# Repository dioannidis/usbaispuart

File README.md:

# USBaispUART

( version 5 )

   A single side, through hole, USBa(i)sp clone, designed in Kicad 5.

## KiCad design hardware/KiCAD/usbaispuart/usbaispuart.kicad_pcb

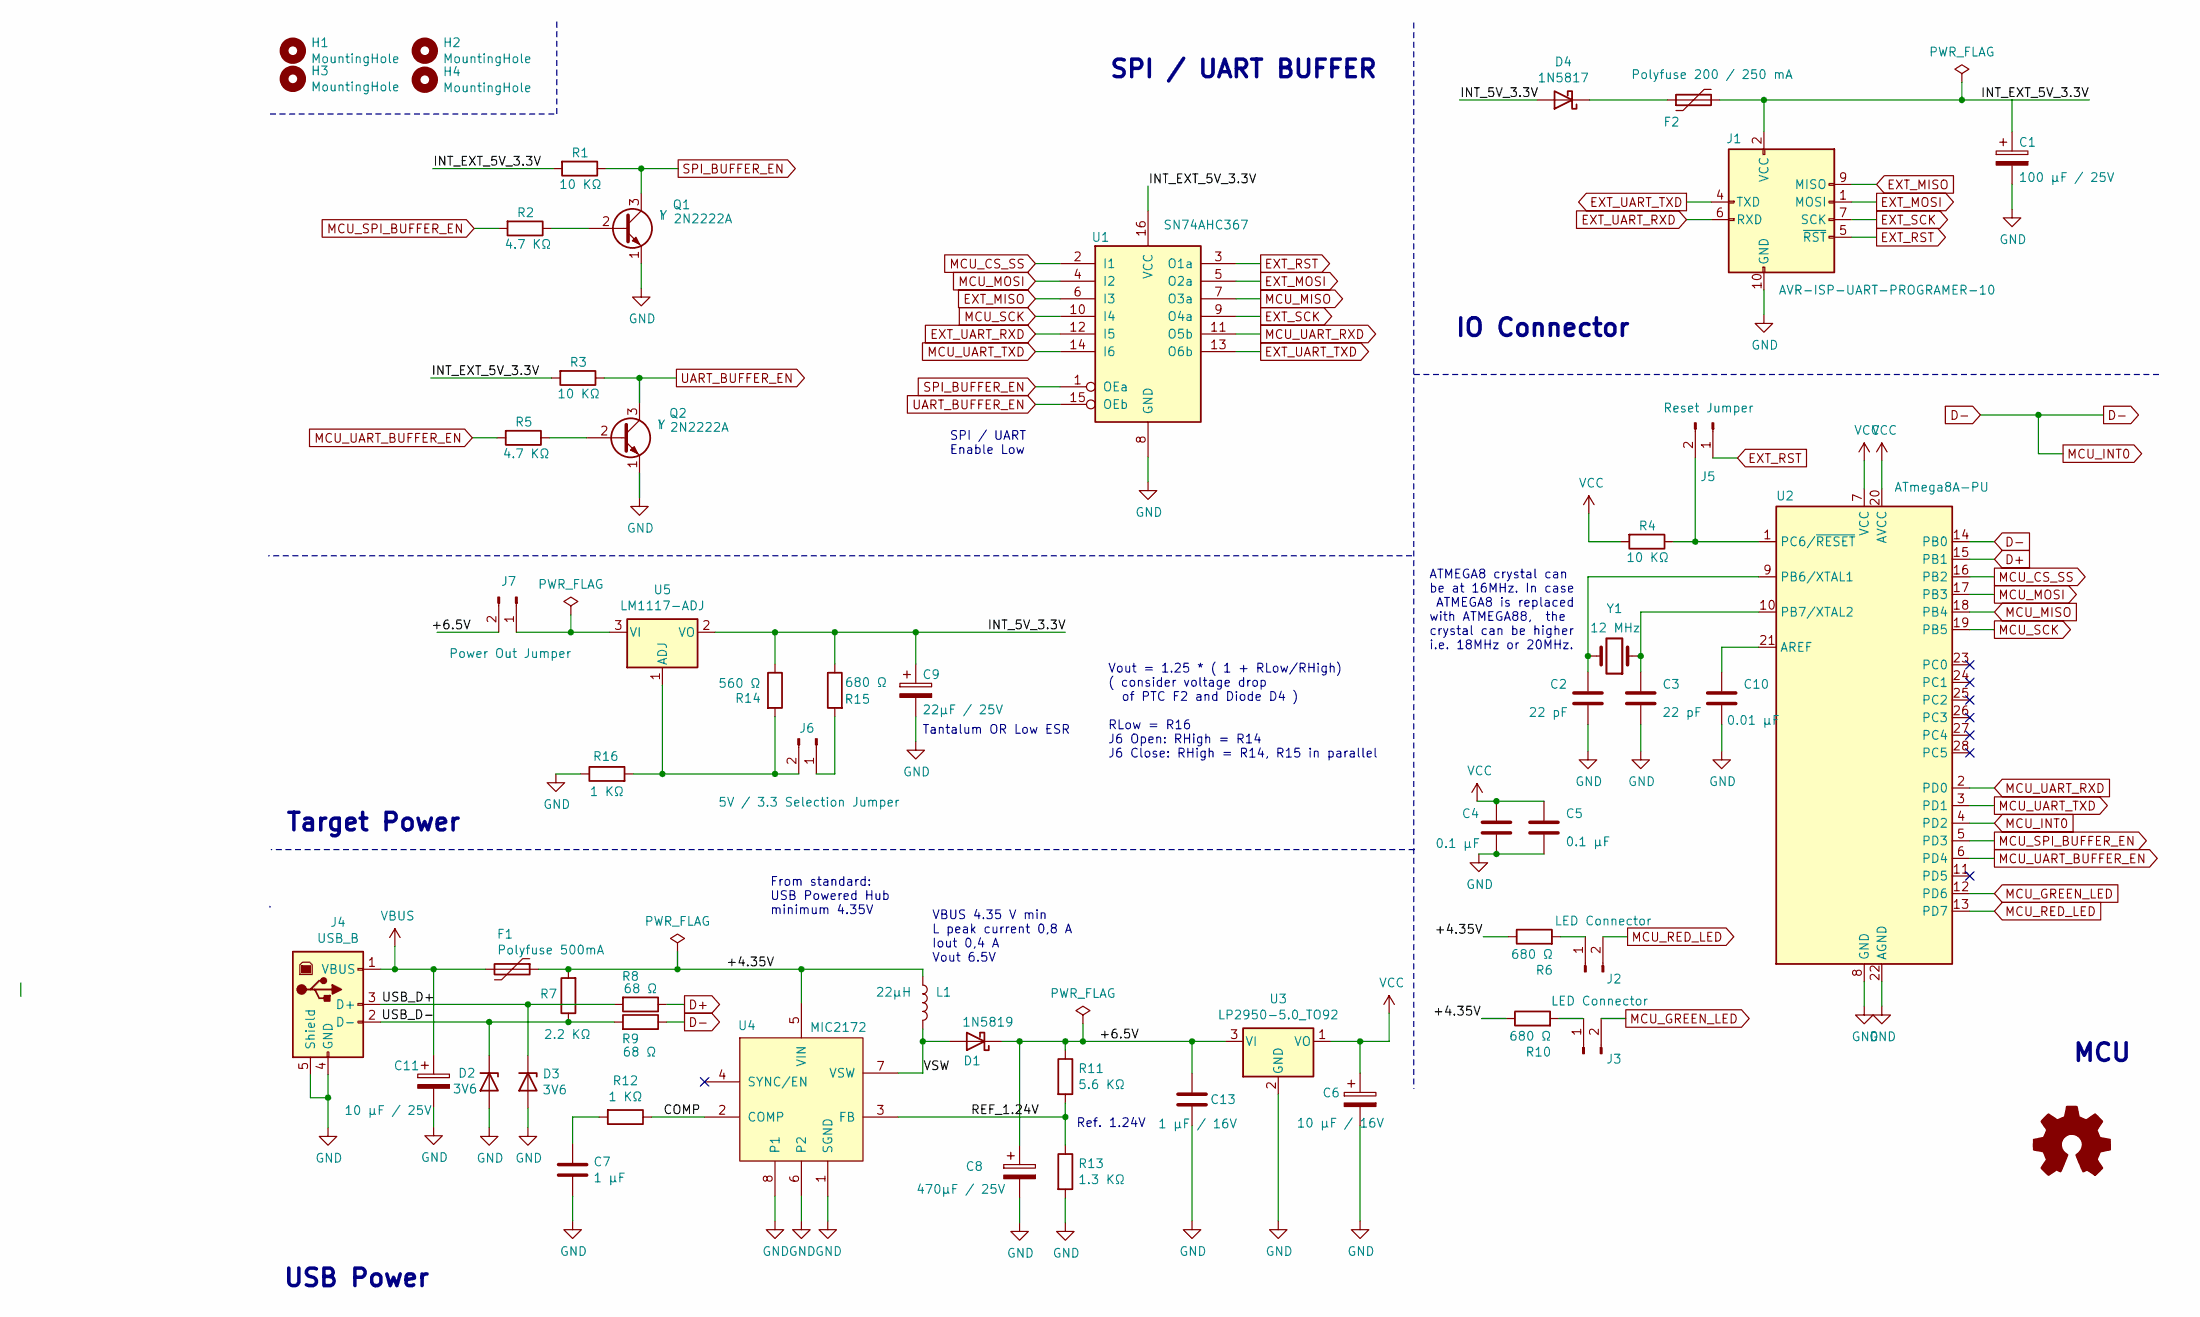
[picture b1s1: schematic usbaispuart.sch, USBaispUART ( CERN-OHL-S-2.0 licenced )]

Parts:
C1: 100 μF / 25V; CP_Radial_D5.0mm_P2.50mm
C2, C3: 22 pF; C_Disc_D4.7mm_W2.5mm_P5.00mm
C4, C5: 0.1 μF; C_Disc_D4.7mm_W2.5mm_P5.00mm
C6: 10 μF / 16V; CP_Radial_D4.0mm_P1.50mm
C7: 1 μF; C_Disc_D4.7mm_W2.5mm_P5.00mm
C8: 470μF / 25V; CP_Radial_D6.3mm_P2.50mm
C9: 22μF / 25V; CP_Radial_Tantal_D5.0mm_P2.50mm
C10: 0.01 μF; C_Disc_D4.7mm_W2.5mm_P5.00mm
C11: 10 μF / 25V; CP_Radial_D4.0mm_P1.50mm
C13: 1 μF / 16V; C_Disc_D4.7mm_W2.5mm_P5.00mm
D1: 1N5819; D_DO-41_SOD81_P2.54mm_Vertical_KathodeUp
D2, D3: 3V6; D_DO-35_SOD27_P5.08mm_Vertical_KathodeUp
D4: 1N5817; D_DO-41_SOD81_P5.08mm_Vertical_KathodeUp
F1: Polyfuse 500mA; Fuse_ECE_RA02560_L7.4mm_W3.1mm
F2: Polyfuse 200 / 250 mA; Fuse_ECE_RA02560_L7.4mm_W3.1mm
H1, H2, H3, H4: MountingHole; MountingHole_3.2mm_M3_DIN965
J1: AVR-ISP-UART-PROGRAMER-10; IDC-Header_2x05_P2.54mm_Horizontal
J2, J3: LED Connector; PinHeader_1x02_P2.54mm_Vertical
J4: USB_B; USB_B_Lumberg_2411_02_Horizontal
J5: Reset Jumper; PinHeader_1x02_P2.54mm_Vertical
J6: 5V / 3.3 Selection Jumper; PinHeader_1x02_P2.54mm_Vertical
J7: Power Out Jumper; PinHeader_1x02_P2.54mm_Vertical
L1: 22μH; L_Radial_D7.0mm_P3.00mm
Q1, Q2: 2N2222A; TO-92_Inline
R1: 10 KΩ; R_Axial_DIN0207_L6.3mm_D2.5mm_P5.08mm_Vertical
R2: 4.7 KΩ; R_Axial_DIN0207_L6.3mm_D2.5mm_P2.54mm_Vertical
R3, R4: 10 KΩ; R_Axial_DIN0207_L6.3mm_D2.5mm_P2.54mm_Vertical
R5: 4.7 KΩ; R_Axial_DIN0207_L6.3mm_D2.5mm_P5.08mm_Vertical
R6, R10, R15: 680 Ω; R_Axial_DIN0207_L6.3mm_D2.5mm_P2.54mm_Vertical
R7: 2.2 KΩ; R_Axial_DIN0207_L6.3mm_D2.5mm_P2.54mm_Vertical
R8, R9: 68 Ω; R_Axial_DIN0207_L6.3mm_D2.5mm_P5.08mm_Vertical
R11: 5.6 KΩ; R_Axial_DIN0207_L6.3mm_D2.5mm_P2.54mm_Vertical
R12, R16: 1 KΩ; R_Axial_DIN0207_L6.3mm_D2.5mm_P2.54mm_Vertical
R13: 1.3 KΩ; R_Axial_DIN0207_L6.3mm_D2.5mm_P2.54mm_Vertical
R14: 560 Ω; R_Axial_DIN0207_L6.3mm_D2.5mm_P2.54mm_Vertical
U1: SN74AHC367; DIP-16_W7.62mm_Socket
U2: ATmega8A-PU; DIP-28_W7.62mm_Socket
U3: LP2950-5.0_TO92; TO-92_Inline
U4: MIC2172; DIP-8_W7.62mm_Socket
U5: LM1117-ADJ; TO-220-3_Vertical
Y1: 12 MHz; Crystal_HC49-4H_Vertical

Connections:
/+4.35V: F1.1, L1.1, R6.1, R7.2, R10.1, U4.5 (VIN)
/+6.5V: C8.1, C13.1, D1.1 (K), J7.2, R11.1, U3.3 (VI)
/COMP: R12.1, U4.2 (COMP)
/INT_5V_3.3V: C9.1, D4.2 (A), R14.1, R15.1, U5.2 (VO)
/INT_EXT_5V_3.3V: C1.1, F2.2, J1.2 (VCC), R1.2, R3.2, U1.16 (VCC)
/REF_1.24V: R11.2, R13.1, U4.3 (FB)
/USB_D+: D3.1 (K), J4.3 (D+), R8.2
/USB_D-: D2.1 (K), J4.2 (D-), R7.1, R9.2
/VSW: D1.2 (A), L1.2, U4.7 (VSW)
D+: R8.1, U2.15 (PB1)
D-: R9.1, U2.4 (PD2), U2.14 (PB0)
EXT_MISO: J1.9 (MISO), U1.6 (I3)
EXT_MOSI: J1.1 (MOSI), U1.5 (O2a)
EXT_RST: J1.5 (~RST), J5.1, U1.3 (O1a)
EXT_SCK: J1.7 (SCK), U1.9 (O4a)
EXT_UART_RXD: J1.6 (RXD), U1.12 (I5)
EXT_UART_TXD: J1.4 (TXD), U1.13 (O6b)
GND: C1.2, C2.2, C3.2, C4.2, C5.2, C6.2, C7.2, C8.2, C9.2, C10.2, C11.2, C13.2, D2.2 (A), D3.2 (A), J1.8 (GND), J1.10 (GND), J4.4 (GND), J4.5 (Shield), Q1.1 (E), Q2.1 (E), R13.2, R16.1, U1.8 (GND), U2.8 (GND), U2.22 (AGND), U3.2 (GND), U4.1 (SGND), U4.6 (P2), U4.8 (P1)
MCU_CS_SS: U1.2 (I1), U2.16 (PB2)
MCU_GREEN_LED: J3.2, U2.12 (PD6)
MCU_MISO: U1.7 (O3a), U2.18 (PB4)
MCU_MOSI: U1.4 (I2), U2.17 (PB3)
MCU_RED_LED: J2.2, U2.13 (PD7)
MCU_SCK: U1.10 (I4), U2.19 (PB5)
MCU_SPI_BUFFER_EN: R2.2, U2.5 (PD3)
MCU_UART_BUFFER_EN: R5.2, U2.6 (PD4)
MCU_UART_RXD: U1.11 (O5b), U2.2 (PD0)
MCU_UART_TXD: U1.14 (I6), U2.3 (PD1)
unnamed: C2.1, U2.9 (PB6/XTAL1), Y1.2
unnamed: C3.1, U2.10 (PB7/XTAL2), Y1.1
unnamed: C7.1, R12.2
unnamed: C10.1, U2.21 (AREF)
unnamed: D4.1 (K), F2.1
unnamed: J2.1, R6.2
unnamed: J3.1, R10.2
unnamed: J5.2, R4.1, U2.1 (PC6/~RESET)
unnamed: J6.1, R15.2
unnamed: J6.2, R14.2, R16.2, U5.1 (ADJ)
unnamed: J7.1, U5.3 (VI)
unnamed: Q1.2 (B), R2.1
unnamed: Q2.2 (B), R5.1
SPI_BUFFER_EN: Q1.3 (C), R1.1, U1.1 (OEa)
UART_BUFFER_EN: Q2.3 (C), R3.1, U1.15 (OEb)
VBUS: C11.1, F1.2, J4.1 (VBUS)
VCC: C4.1, C5.1, C6.1, R4.2, U2.7 (VCC), U2.20 (AVCC), U3.1 (VO)

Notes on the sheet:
Ref. 1.24V
USB Power
MCU
SPI / UART BUFFER
IO Connector
VBUS 4.35 V min L peak current 0,8 A Iout 0,4 A Vout 6.5V
ATMEGA8 crystal can be at 16MHz. In case ATMEGA8 is replaced with ATMEGA88, the crystal can be higher i.e. 18MHz or 20MHz.
From standard: USB Powered Hub minimum 4.35V
Target Power
SPI / UART Enable Low
Vout = 1.25 * ( 1 + RLow/RHigh) ( consider voltage drop of PTC F2 and Diode D4 ) RLow = R16 J6 Open: RHigh = R14 J6 Close: RHigh = R14, R15 in parallel
Tantalum OR Low ESR

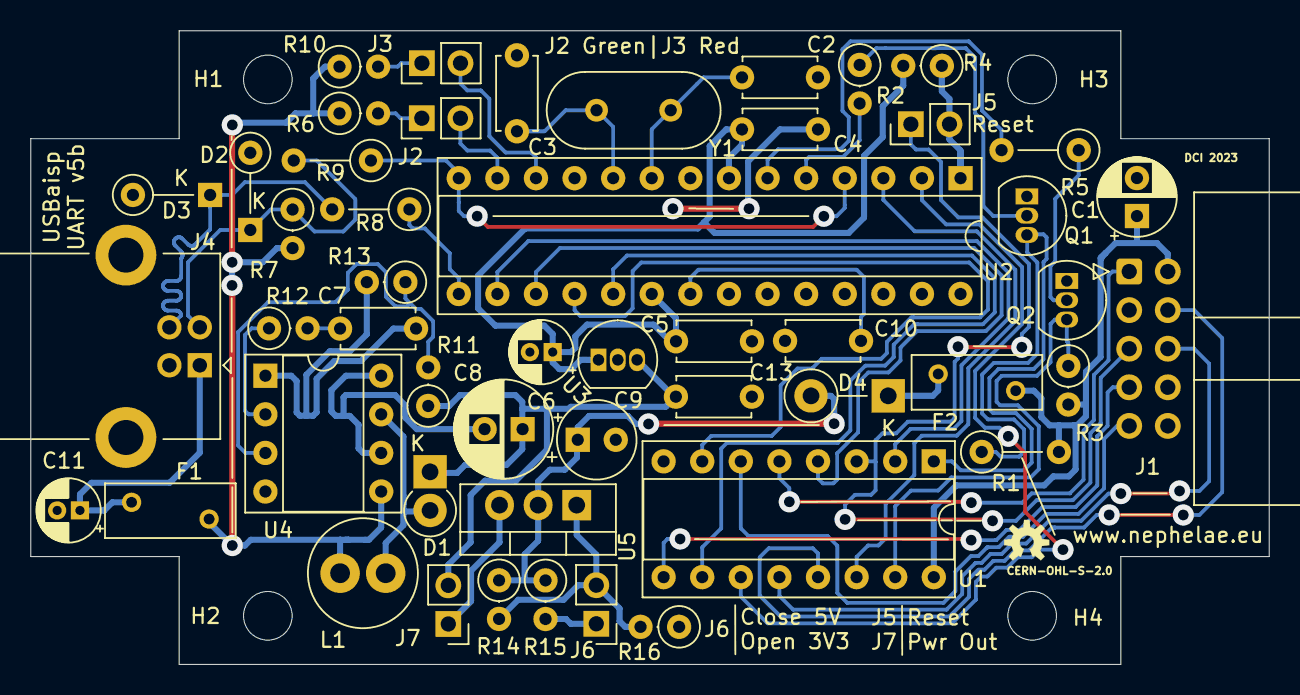
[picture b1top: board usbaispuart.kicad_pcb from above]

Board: 2 copper layers, 81.5 x 41.7 mm, 54 parts (0 on the bottom side), 45 nets.

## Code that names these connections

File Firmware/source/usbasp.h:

/*
 * usbasp.c - part of USBasp
 *
 * Autor..........: Thomas Fischl <tfischl@gmx.de>
 * Description....: Definitions and macros for usbasp
 * Licence........: GNU GPL v2 (see Readme.txt)
 * Creation Date..: 2009-02-28
 * Last change....: 2009-02-28
 */

#ifndef USBASP_H_
#define USBASP_H_

/* USB function call identifiers */
// ISP:
#define USBASP_FUNC_CONNECT             1
#define USBASP_FUNC_DISCONNECT          2
#define USBASP_FUNC_TRANSMIT            3
#define USBASP_FUNC_READFLASH           4
#define USBASP_FUNC_ENABLEPROG          5
#define USBASP_FUNC_WRITEFLASH          6
#define USBASP_FUNC_READEEPROM          7
#define USBASP_FUNC_WRITEEEPROM         8
#define USBASP_FUNC_SETLONGADDRESS      9
#define USBASP_FUNC_SETISPSCK           10
// TPI:
#define USBASP_FUNC_TPI_CONNECT         11
#define USBASP_FUNC_TPI_DISCONNECT      12
#define USBASP_FUNC_TPI_RAWREAD         13
#define USBASP_FUNC_TPI_RAWWRITE        14
#define USBASP_FUNC_TPI_READBLOCK       15
#define USBASP_FUNC_TPI_WRITEBLOCK      16
#define USBASP_FUNC_GETCAPABILITIES     127
// UART:
#define USBASP_FUNC_UART_CONFIG         60
#define USBASP_FUNC_UART_DISABLE        63

/* USBASP capabilities */
#define USBASP_CAP_0_TPI                0x01
#define USBASP_CAP_6_UART               0x40
#define USBASP_CAP_HIDUART              0x80

#define USBASP_CAP_12MHZ_CLOCK          0x00
#define USBASP_CAP_16MHZ_CLOCK          0x01
#define USBASP_CAP_18MHZ_CLOCK          0x02
#define USBASP_CAP_20MHZ_CLOCK          0x03

/* programming state */
#define PROG_STATE_IDLE                 0
#define PROG_STATE_WRITEFLASH           1
#define PROG_STATE_READFLASH            2
#define PROG_STATE_READEEPROM           3
#define PROG_STATE_WRITEEEPROM          4
#define PROG_STATE_TPI_READ             5
#define PROG_STATE_TPI_WRITE            6
#define PROG_STATE_SET_REPORT           7

/* Block mode flags */
#define PROG_BLOCKFLAG_FIRST            1
#define PROG_BLOCKFLAG_LAST             2

/* ISP SCK speed identifiers */
#define USBASP_ISP_SCK_AUTO             0
#define USBASP_ISP_SCK_0_5              1   /* 500 Hz */
#define USBASP_ISP_SCK_1                2   /*   1 kHz */
#define USBASP_ISP_SCK_2                3   /*   2 kHz */
#define USBASP_ISP_SCK_4                4   /*   4 kHz */
#define USBASP_ISP_SCK_8                5   /*   8 kHz */
#define USBASP_ISP_SCK_16               6   /*  16 kHz */
#define USBASP_ISP_SCK_32               7   /*  32 kHz */
#define USBASP_ISP_SCK_93_75            8   /*  93.75 kHz */
#define USBASP_ISP_SCK_187_5            9   /* 187.5  kHz */
#define USBASP_ISP_SCK_375              10  /* 375 kHz   */
#define USBASP_ISP_SCK_750              11  /* 750 kHz   */
#define USBASP_ISP_SCK_1500             12  /* 1.5 MHz   */
#define USBASP_ISP_SCK_3000             13  /* 3 MHz   */

// UART flags.
#define USBASP_UART_PARITY_MASK         0b11
#define USBASP_UART_PARITY_NONE         0b00
#define USBASP_UART_PARITY_EVEN         0b01
#define USBASP_UART_PARITY_ODD          0b10

#define USBASP_UART_STOP_MASK           0b100
#define USBASP_UART_STOP_1BIT           0b000
#define USBASP_UART_STOP_2BIT           0b100

#define USBASP_UART_BYTES_MASK          0b111000
#define USBASP_UART_BYTES_5B            0b000000
#define USBASP_UART_BYTES_6B            0b001000
#define USBASP_UART_BYTES_7B            0b010000
#define USBASP_UART_BYTES_8B            0b011000
#define USBASP_UART_BYTES_9B            0b100000

/* macros for gpio functions */
/* LEDs are active low */
#define ledRedOff()                     DDRD &= ~(1 << PD6)
#define ledRedOn()                      DDRD |= (1 << PD6)
#define ledGreenOff()                   DDRD &= ~(1 << PD7)
#define ledGreenOn()                    DDRD |= (1 << PD7)

/* macros for ISP, UART buffer functions */
#define ISPBufferOff()                  PORTD &= ~(1 << PD3)
#define ISPBufferOn()                   PORTD |= (1 << PD3)
#define UARTBufferOff()                 PORTD &= ~(1 << PD4)
#define UARTBufferOn()                  PORTD |= (1 << PD4)

#endif /* USBASP_H_ */

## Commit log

2022-08-16 Create LICENSE.md
    CERN-OHL-S-2.0
2022-08-16 Add usbaispuart hardware files.
2022-08-16 initial import
2022-08-17 Repository refactoring ....
2022-12-30 Fixed an error on 2N2222A symbol.
    + Added 2N2222A datasheet.
    + Regenerate PCB images.
2022-12-30 Bump to version 5
2022-12-30 Actual add forgotten 2N2222A datasheet
2022-12-30 Change D4 from 1N5819 to the correct 1N5817
2022-12-30 Regenerate schematic PDF
2022-12-30 Fixed silkscreen.
    + Regenerate gerber files.
2022-12-30 Regenerate PCB images.
2023-01-04 Bump version to 5a. + Fix an error trace. + Change C6 capacitor to electrolytic. + Rearrange layout to reduce noise.
2023-05-03 Update firmware to 1.11 pre-release from https://github.com/dioannidis/usbasp
2023-05-03 Update to 5b
2023-05-03 Add USBaisp assembled device image
2023-06-06 Increase polling interval of the second hid interface .
2023-06-06 Disabling the doubling SCK clock speed after PE fixes the read errors. Need to investigate more
2023-06-06 Misc
